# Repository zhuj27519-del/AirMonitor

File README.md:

# AirMonitor

环境监测器工程恢复与归档，整理日期：2026-11-12。统一工作目录：`D:\Projects\AirMonitor`。

## 原型机实拍

用户提供的 V4 原型机照片，拍摄日期及对应固件提交待确认。照片中可见 ONLINE 和各项读数；不代表测量精度或全部硬件验收已通过。更多照片见 [实物与装配记录](docs/images/prototype-v4/README.md)。

## 当前主源码

`src/AirMonitor/AirMonitor.ino` 原样恢复自 `AirMonitor_V4_9Text_Matched`，为 ESP8266 + HF035 九文本控件方案。选择依据为源码中明确的 0..8 页面控件映射和接线；不是仅按文件修改时间选择。它是待实物验证的工作基线，不代表已经量产或通过实测。

2026-11-12 使用本机 Arduino CLI、ESP8266 core 3.1.2、`esp8266:esp8266:nodemcuv2` 编译成功：RAM 28856/80192，IRAM 61895/65536，Flash 242752/1048576 字节。未烧录设备。

依赖 Arduino core 自带 Arduino.h、Wire（OLED 历史版）、EspSoftwareSerial；主源码未使用 Wi-Fi，也没有配置 Wi-Fi 密码。裸 ESP-12F 与 NodeMCU 不是同一种开发板：当前 D 引脚别名按 NodeMCU 定义，裸模块的启动电阻、电源、烧录方式需要核对。

## 配置与状态

|模块|主源码配置|证据及限制|
|---|---|---|
|ESP8266 / ESP-12F|按 NodeMCU ESP-12E 板型构建|模块型号来自任务；实际板载模块未现场确认|
|PMS7003M|TX→D5/GPIO14，9600 8N1|32 字节协议，读取大气环境 PM 字段；需真实帧验证|
|21VOC|TX→D6/GPIO12，9600 8N1|12 字节 0x2C 帧；负温度与量纲待核对|
|HF035|GPIO1 TX 输出，115200，212×318，sGUI 文本 ID 0..8|屏端 TX 标签含义需要按实际方向核实，不能仅凭标签将两个输出相连|
|OLED 历史方案|SDA D2/GPIO4，SCL D1/GPIO5|独立历史固件；不是当前 HF035 配置|

LCD/PMS 的 5V 供电说明来自历史代码；ESP8266 GPIO 为 3.3V 逻辑，实际信号电平和共地应核实。eCO2 是估算值，HCHO 是模块报告值。

发现的 STM32G0B1 + ST7789 分支、V1 首板与 KiCad 草稿分别归档，不能直接用于 ESP8266。历史硬件资料中的 NO-GO / DO NOT FABRICATE 状态仍有效。

## 开发

```powershell
arduino-cli core install esp8266:esp8266@3.1.2 --additional-urls https://arduino.esp8266.com/stable/package_esp8266com_index.json
arduino-cli compile --fqbn esp8266:esp8266:nodemcuv2 src/AirMonitor
```

本机验证使用已有 Arduino IDE 附带的 CLI 与 `.arduinoIDE/arduino-cli.yaml`，无需重装。构建不是硬件验收。IRAM 使用率 94%，增加功能前检查余量。

参见 [项目结构](docs/STRUCTURE.md)、[历史版本](docs/VERSIONS.md)、[检查报告](docs/AUDIT.md)、[TODO](TODO.md)。`docs/inventory.json` 记录来源、SHA-256 和目标路径；`docs/duplicates.json` 记录内容相同的文件。

原始目录未移动、未删除。压缩包、旧 Git bundle、订单 PDF、构建产物只在本地保留并排除 Git，避免未经检查的归档内容或订单隐私进入仓库。历史 CAD 工程保留目录完整性，不将共享文件强行合并。

## GitHub

公开仓库：https://github.com/zhuj27519-del/AirMonitor 。主分支为 main。首次上传已核对 commit SHA 与 tree SHA 一致；完整原始归档仍仅本地保存。

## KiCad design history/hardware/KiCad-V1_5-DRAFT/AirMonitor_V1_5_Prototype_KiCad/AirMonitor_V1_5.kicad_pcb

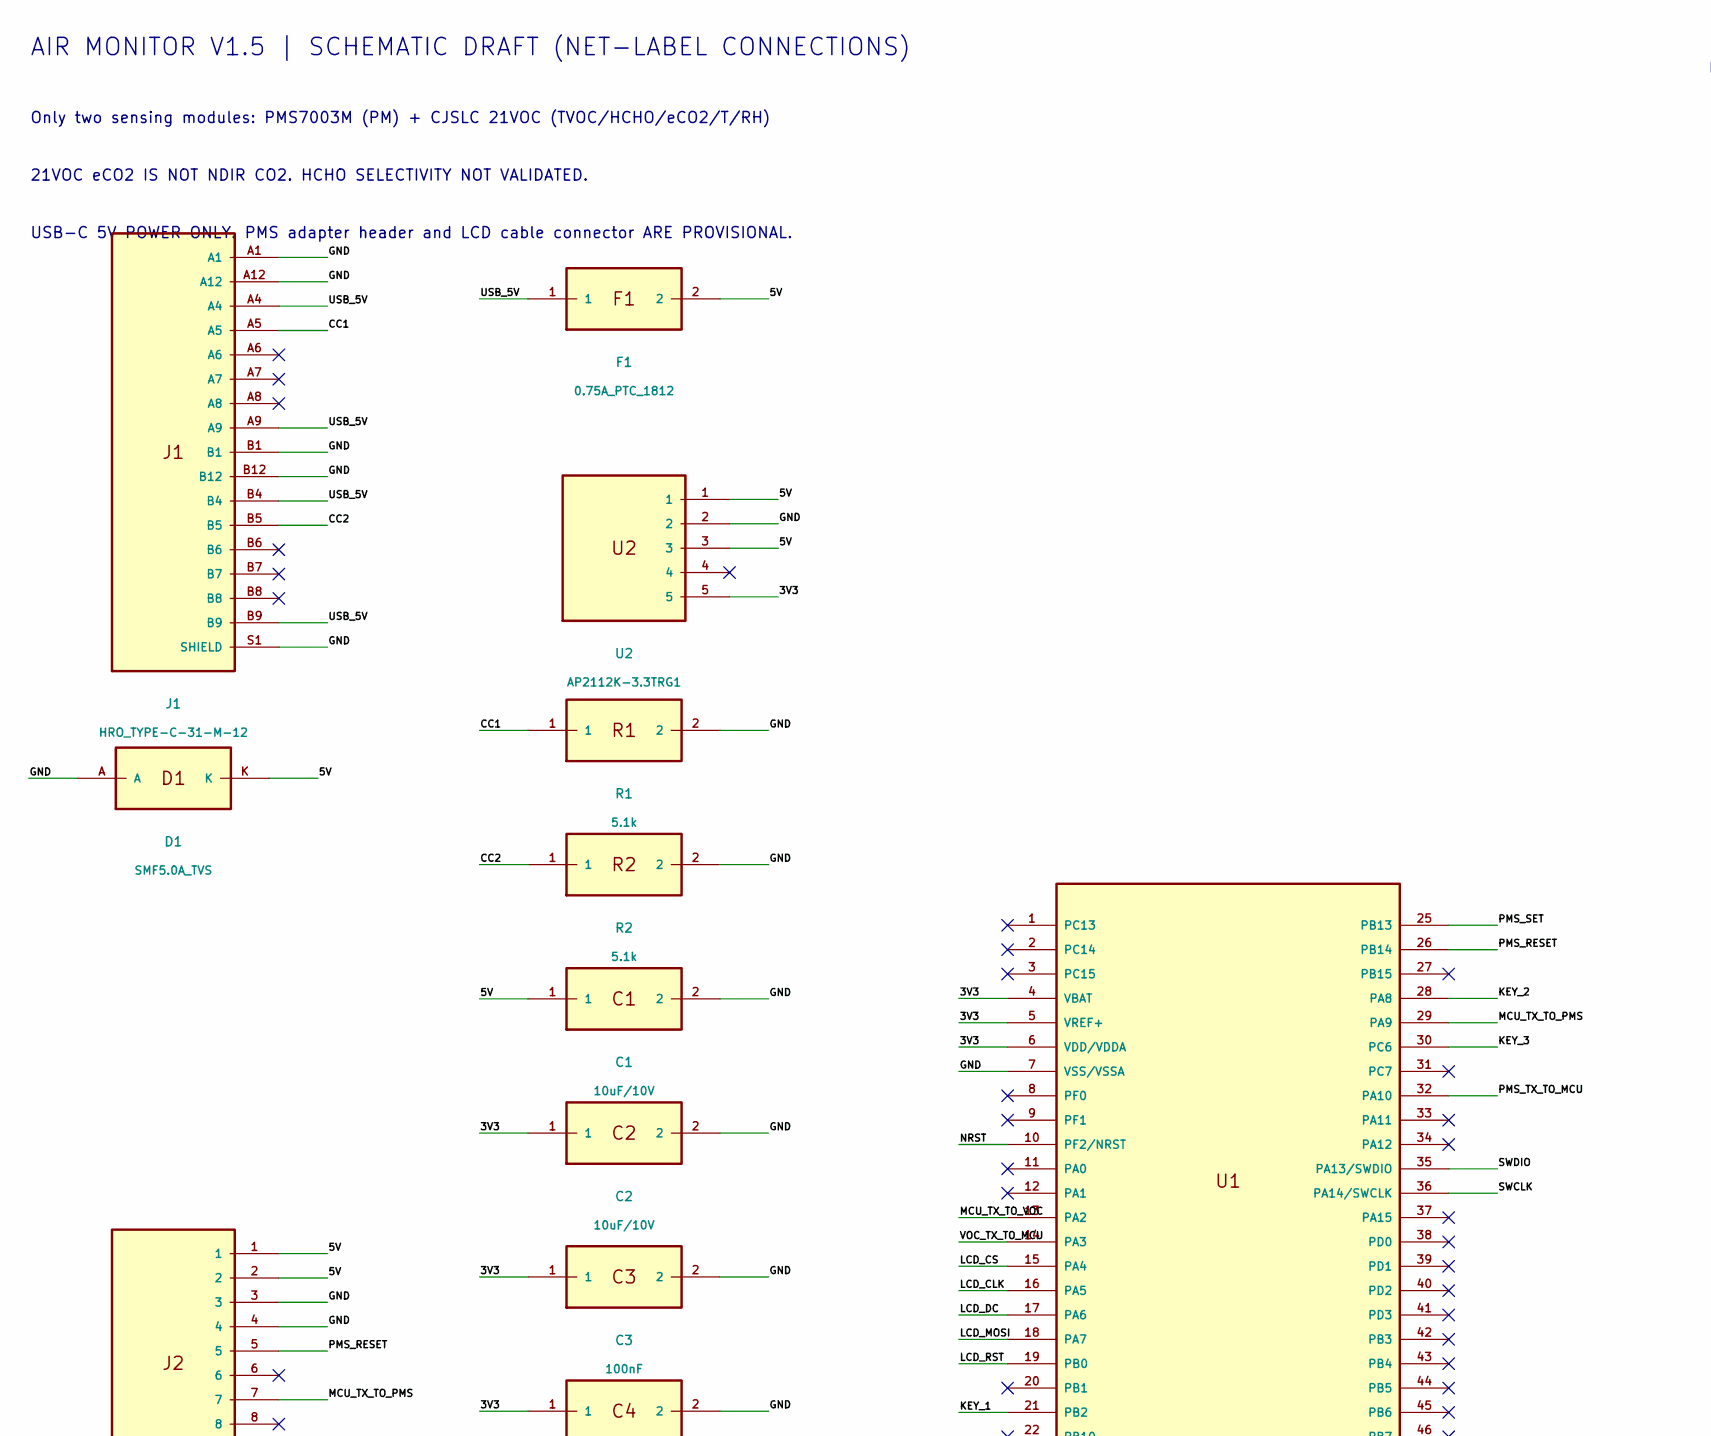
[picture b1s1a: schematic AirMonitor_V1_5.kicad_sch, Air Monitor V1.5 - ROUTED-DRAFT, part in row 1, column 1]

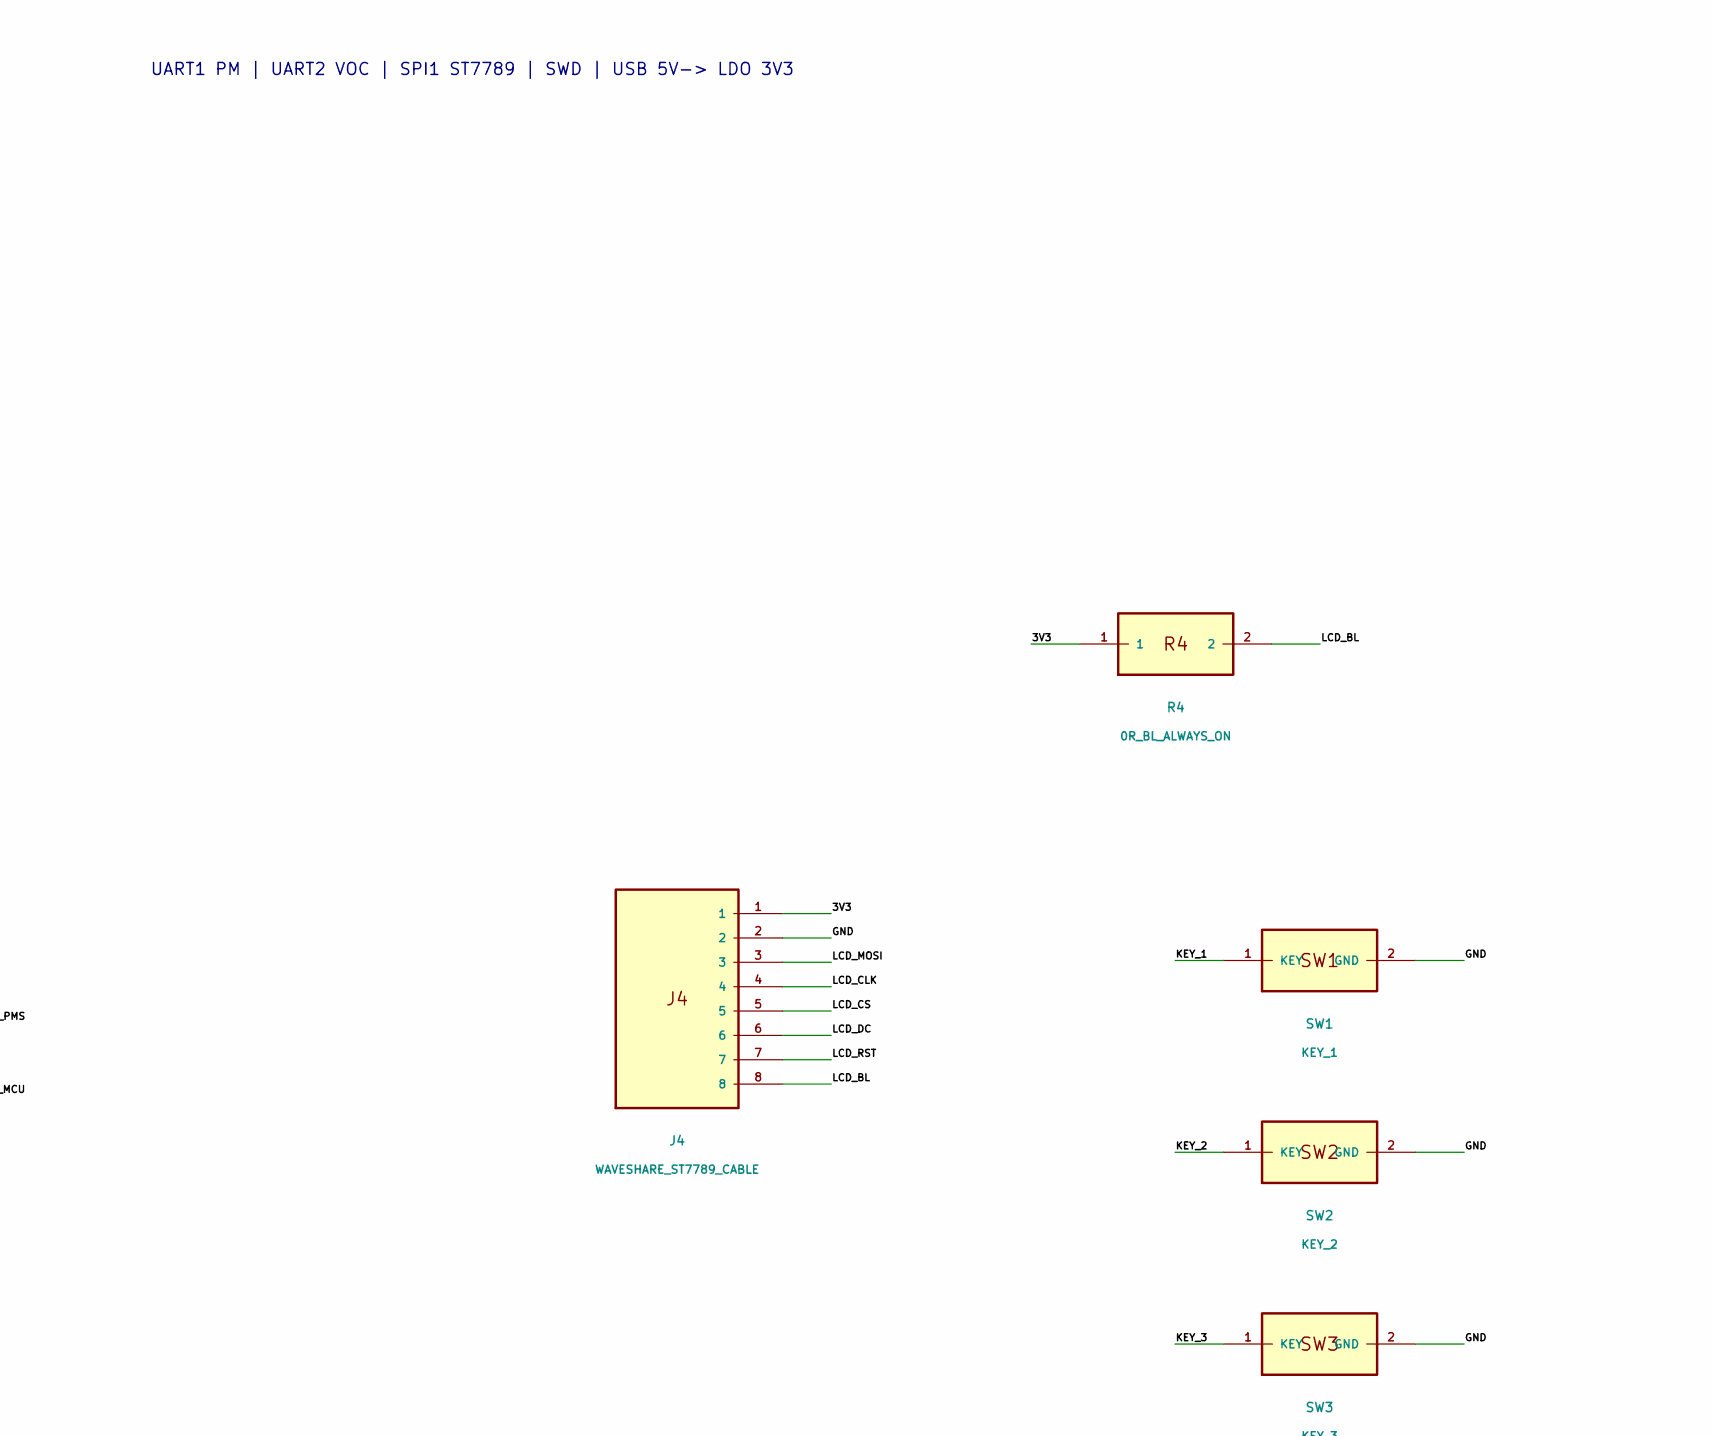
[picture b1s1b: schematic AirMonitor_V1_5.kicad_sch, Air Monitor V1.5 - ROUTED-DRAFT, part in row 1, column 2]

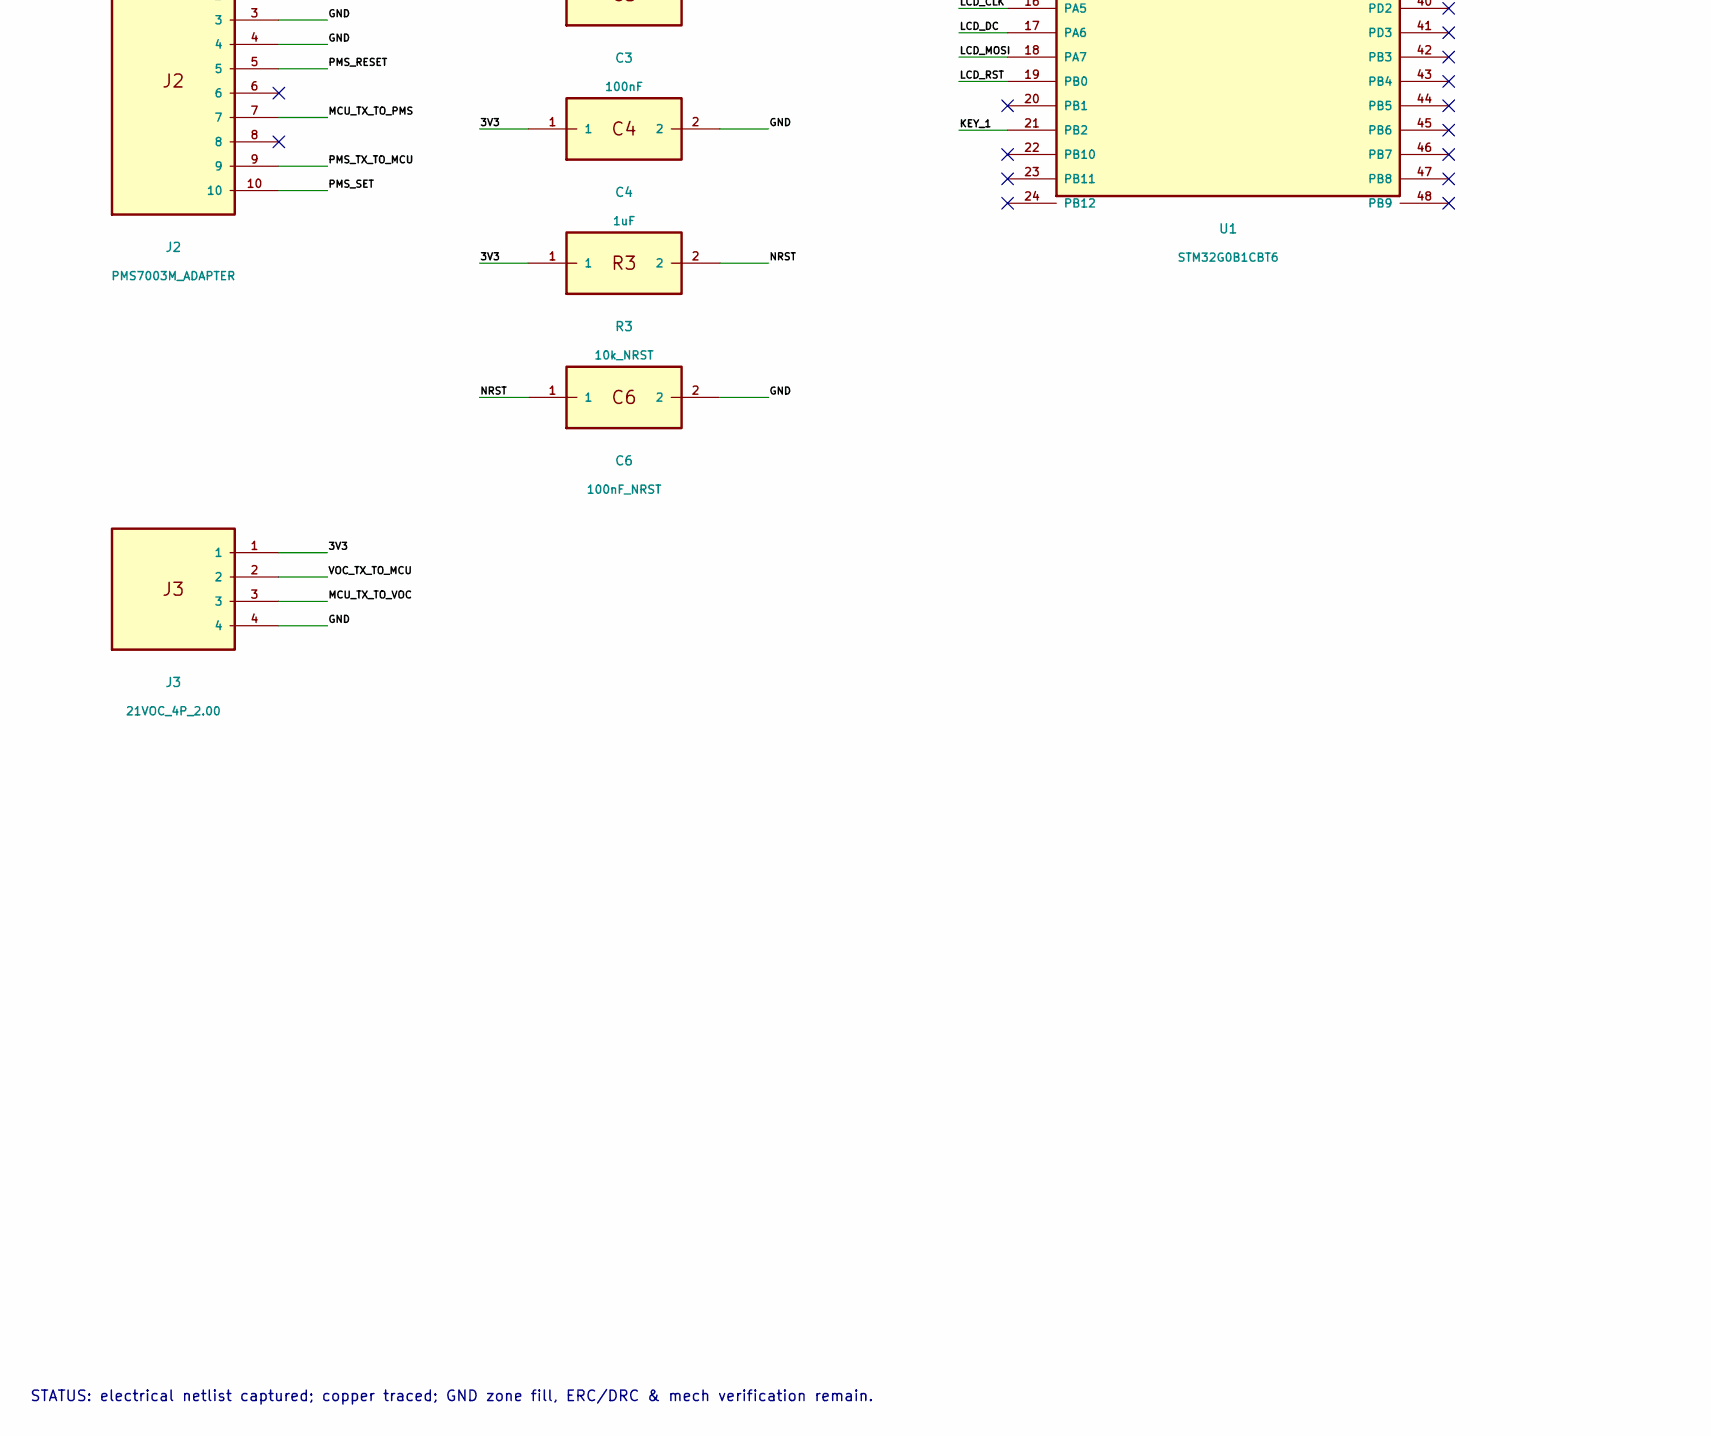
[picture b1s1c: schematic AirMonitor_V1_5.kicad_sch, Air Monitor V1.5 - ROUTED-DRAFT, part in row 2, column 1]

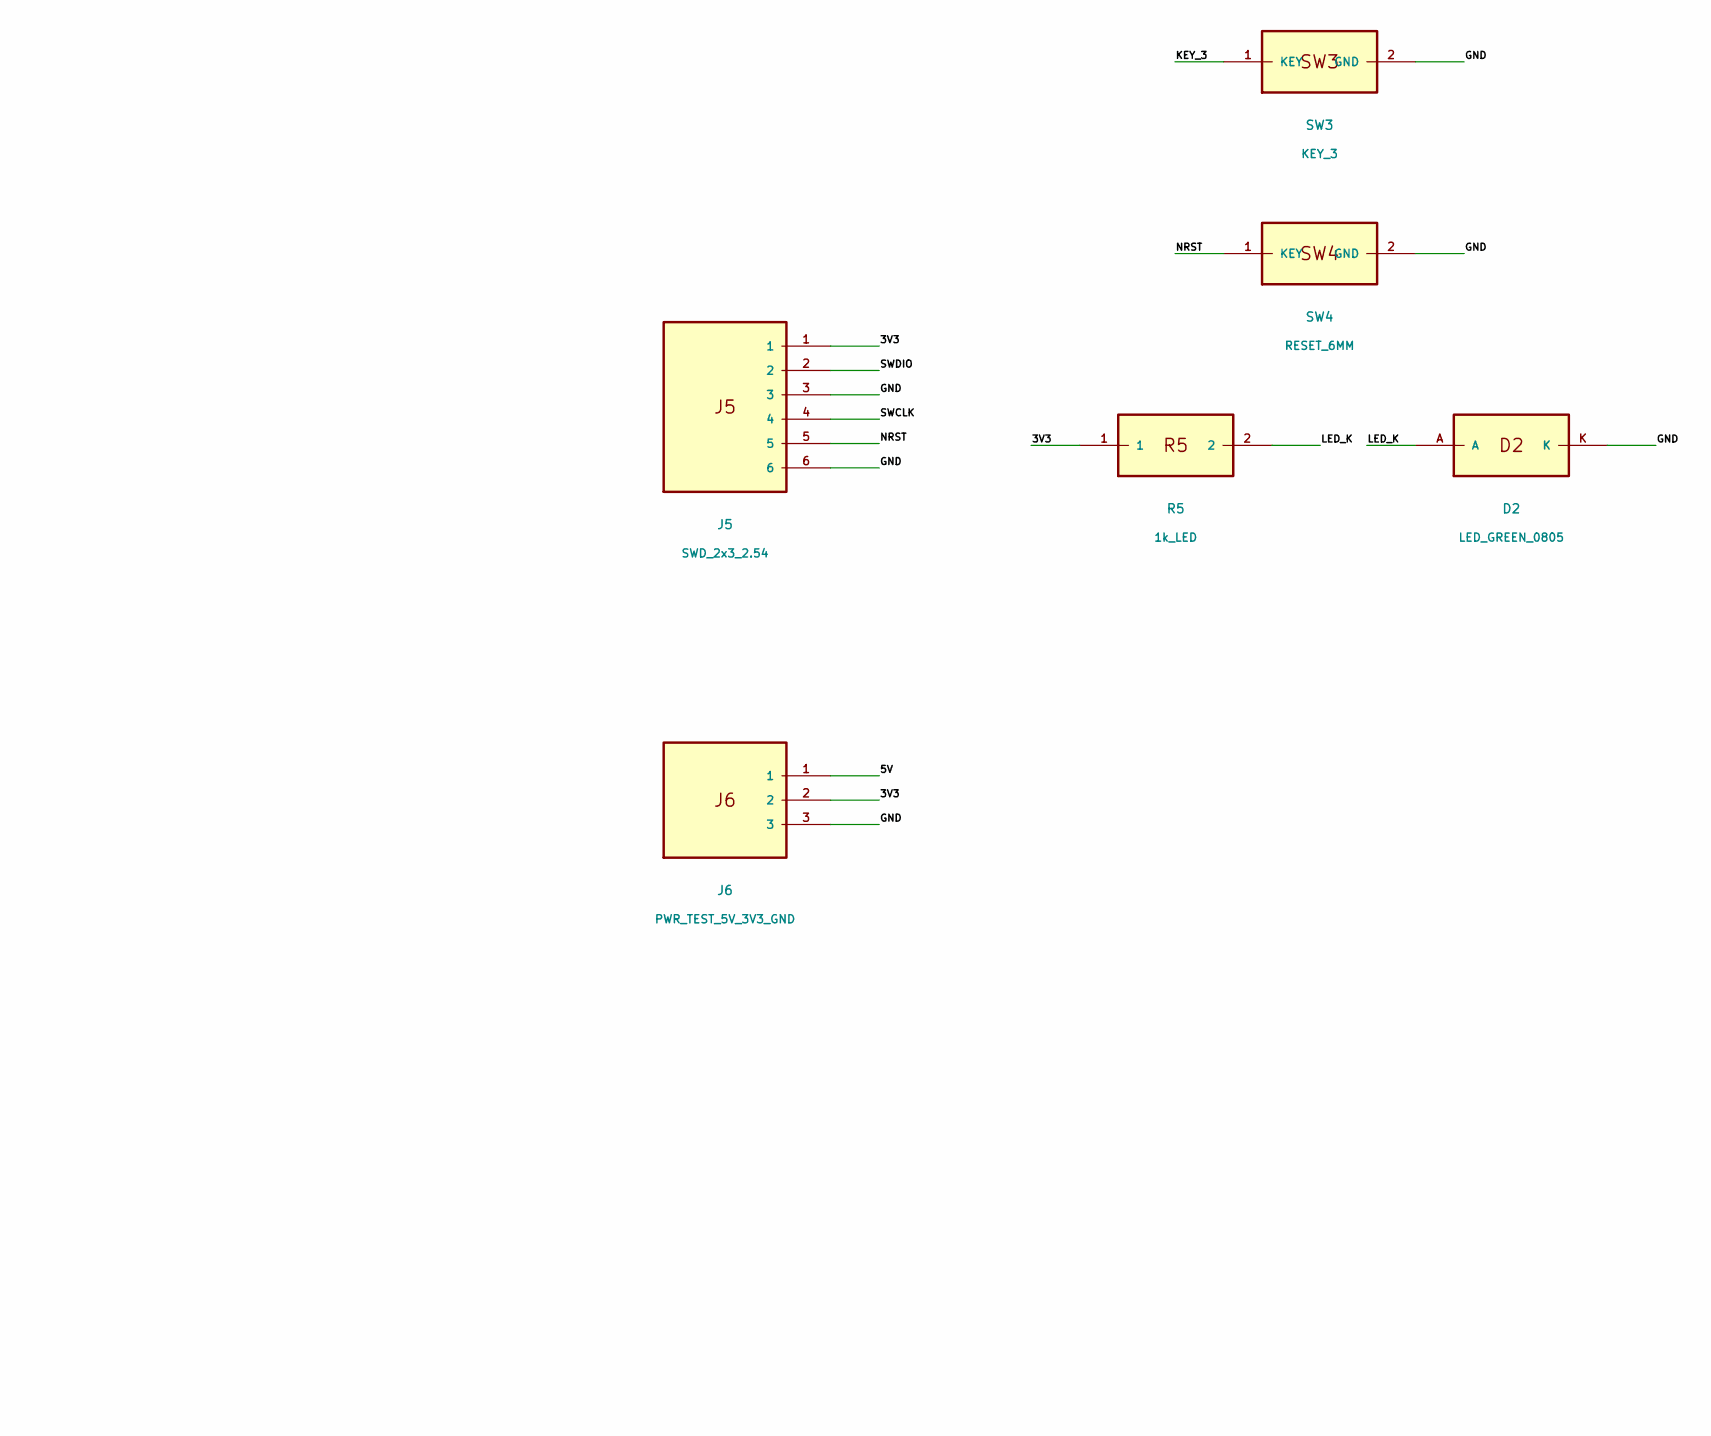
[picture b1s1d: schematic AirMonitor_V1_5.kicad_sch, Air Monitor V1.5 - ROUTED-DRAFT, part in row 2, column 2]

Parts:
C1, C2: 10uF/10V; 0805
C3: 100nF; 0805
C4: 1uF; 0805
C6: 100nF_NRST; 0805
D1: SMF5.0A_TVS; SOD123
D2: LED_GREEN_0805; LED_0805
F1: 0.75A_PTC_1812; 1812
J1: HRO_TYPE-C-31-M-12; USB_C_HRO
J2: PMS7003M_ADAPTER; PinHeader_2x05_2.54
J3: 21VOC_4P_2.00; PinHeader_1x04_2.00
J4: WAVESHARE_ST7789_CABLE; PinHeader_1x08_2.00
J5: SWD_2x3_2.54; PinHeader_2x03_2.54
J6: PWR_TEST_5V_3V3_GND; PinHeader_1x03_2.54
R1, R2: 5.1k; 0805
R3: 10k_NRST; 0805
R4: 0R_BL_ALWAYS_ON; 0805
R5: 1k_LED; 0805
SW1: KEY_1; SW_6x6mm_THT
SW2: KEY_2; SW_6x6mm_THT
SW3: KEY_3; SW_6x6mm_THT
SW4: RESET_6MM; SW_6x6mm_THT
U1: STM32G0B1CBT6; LQFP48_7x7_P0.5
U2: AP2112K-3.3TRG1; SOT23_5

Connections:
3V3: C2.1, C3.1, C4.1, J3.1, J4.1, J5.1, J6.2, R3.1, R4.1, R5.1, U1.4 (VBAT), U1.5 (VREF+), U1.6 (VDD/VDDA), U2.5
5V: C1.1, D1.K, F1.2, J2.1, J2.2, J6.1, U2.1, U2.3
CC1: J1.A5, R1.1
CC2: J1.B5, R2.1
GND: C1.2, C2.2, C3.2, C4.2, C6.2, D1.A, D2.K, J1.A1, J1.A12, J1.B1, J1.B12, J1.S1 (SHIELD), J2.3, J2.4, J3.4, J4.2, J5.3, J5.6, J6.3, R1.2, R2.2, SW1.2 (GND), SW2.2 (GND), SW3.2 (GND), SW4.2 (GND), U1.7 (VSS/VSSA), U2.2
KEY_1: SW1.1 (KEY), U1.21 (PB2)
KEY_2: SW2.1 (KEY), U1.28 (PA8)
KEY_3: SW3.1 (KEY), U1.30 (PC6)
LCD_BL: J4.8, R4.2
LCD_CLK: J4.4, U1.16 (PA5)
LCD_CS: J4.5, U1.15 (PA4)
LCD_DC: J4.6, U1.17 (PA6)
LCD_MOSI: J4.3, U1.18 (PA7)
LCD_RST: J4.7, U1.19 (PB0)
LED_K: D2.A, R5.2
MCU_TX_TO_PMS: J2.7, U1.29 (PA9)
MCU_TX_TO_VOC: J3.3, U1.13 (PA2)
NRST: C6.1, J5.5, R3.2, SW4.1 (KEY), U1.10 (PF2/NRST)
PMS_RESET: J2.5, U1.26 (PB14)
PMS_SET: J2.10, U1.25 (PB13)
PMS_TX_TO_MCU: J2.9, U1.32 (PA10)
SWCLK: J5.4, U1.36 (PA14/SWCLK)
SWDIO: J5.2, U1.35 (PA13/SWDIO)
USB_5V: F1.1, J1.A4, J1.A9, J1.B4, J1.B9
VOC_TX_TO_MCU: J3.2, U1.14 (PA3)

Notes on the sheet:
AIR MONITOR V1.5 | SCHEMATIC DRAFT (NET-LABEL CONNECTIONS)
Only two sensing modules: PMS7003M (PM) + CJSLC 21VOC (TVOC/HCHO/eCO2/T/RH)
21VOC eCO2 IS NOT NDIR CO2. HCHO SELECTIVITY NOT VALIDATED.
USB-C 5V POWER ONLY. PMS adapter header and LCD cable connector ARE PROVISIONAL.
STATUS: electrical netlist captured; copper traced; GND zone fill, ERC/DRC & mech verification remain.
UART1 PM | UART2 VOC | SPI1 ST7789 | SWD | USB 5V-> LDO 3V3

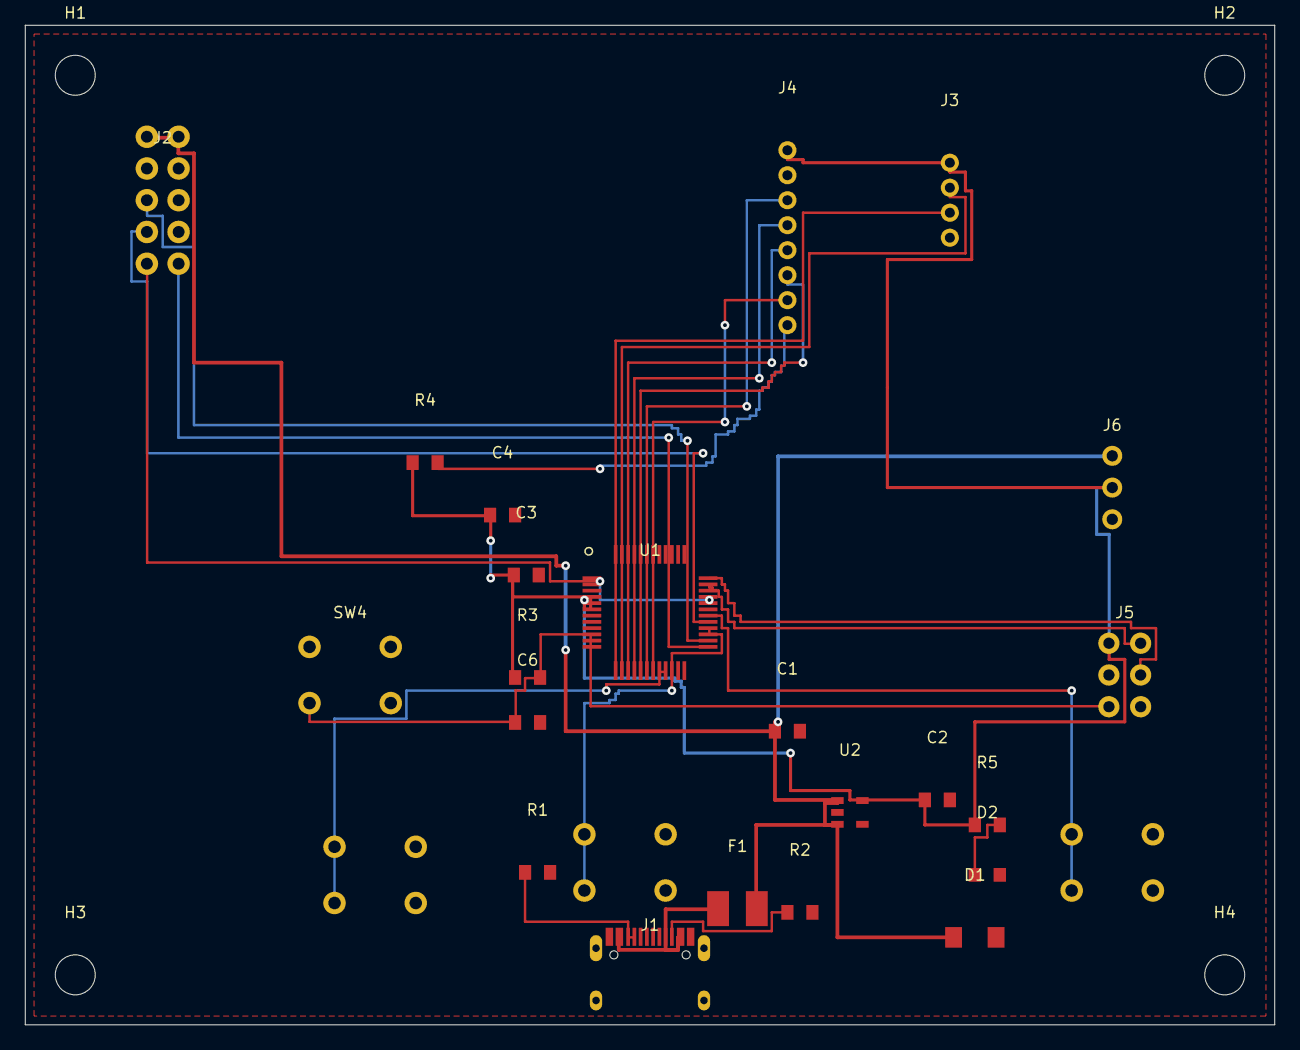
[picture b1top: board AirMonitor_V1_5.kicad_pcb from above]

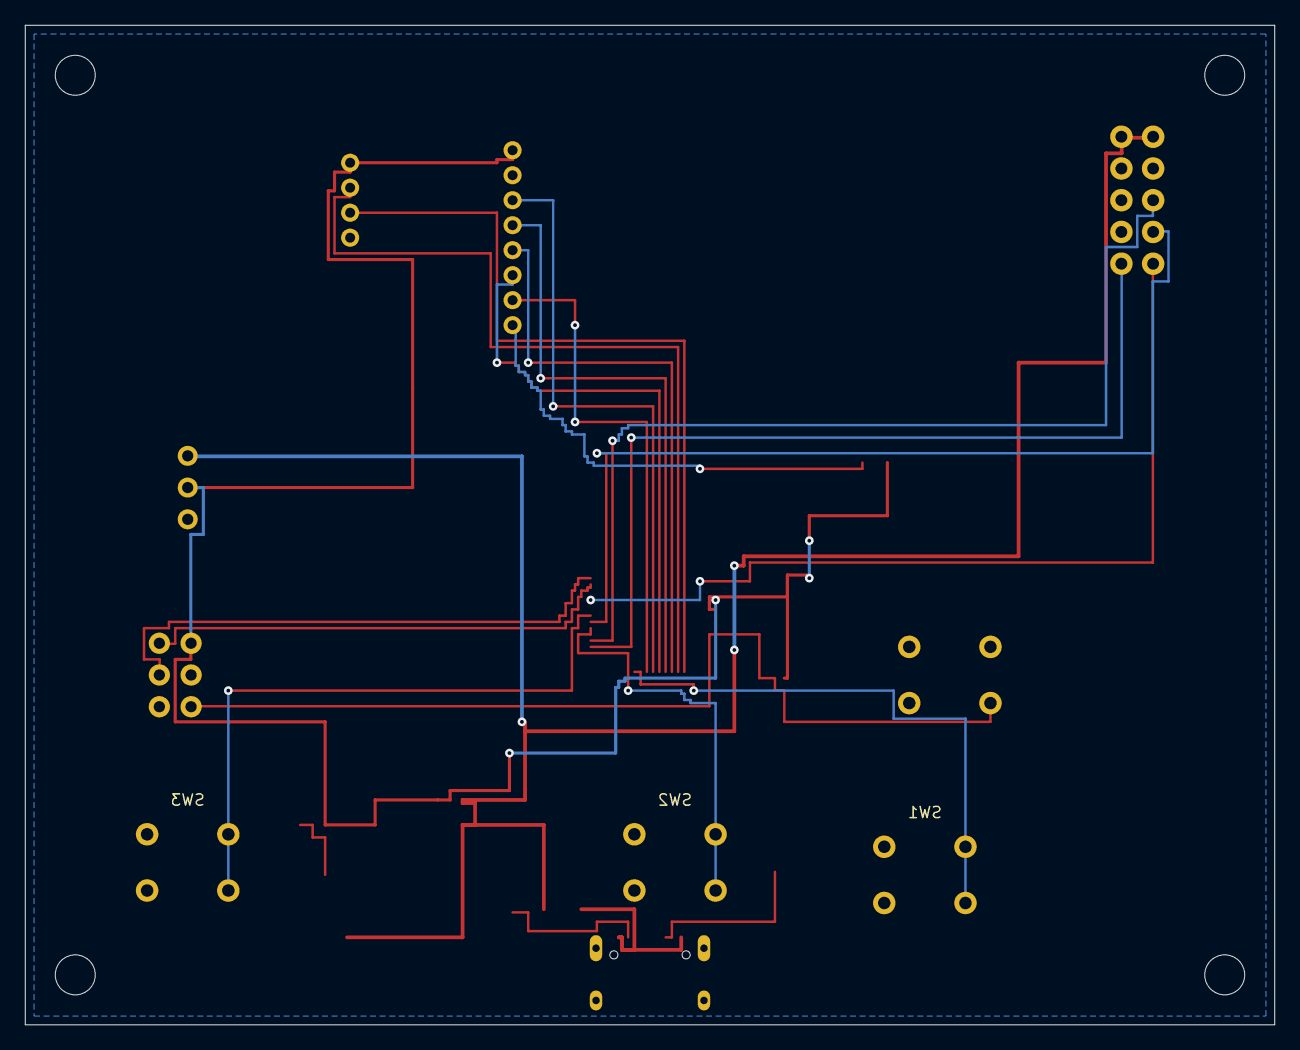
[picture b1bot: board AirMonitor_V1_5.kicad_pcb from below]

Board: 2 copper layers, 100.0 x 80.0 mm, 29 parts (3 on the bottom side), 25 nets.

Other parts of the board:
H1, H2, H3, H4: M3_NPTH; MountingHole_3.2

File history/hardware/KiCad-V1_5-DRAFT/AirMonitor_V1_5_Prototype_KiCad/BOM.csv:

Ref,Value,Footprint,Qty,Engineering note
U1,STM32G0B1CBT6,AirMonitor:LQFP48_7x7_P0.5,1,"STM32G0B1CBT6 (GP non-N) LQFP48 pinout cross-referenced against ST DS13560 Rev6 Fig5, VDD/VDDA, VBAT, VREF+ explicitly powered."
J1,HRO_TYPE-C-31-M-12,AirMonitor:USB_C_HRO,1,USB-C 5V power-only; verify HRO contact land-pattern against specific purchased connector. CURRENT PAD MODEL IS PROVISIONAL!
F1,0.75A_PTC_1812,AirMonitor:1812,1,
R1,5.1k,AirMonitor:0805,1,
R2,5.1k,AirMonitor:0805,1,
U2,AP2112K-3.3TRG1,AirMonitor:SOT23_5,1,
C1,10uF/10V,AirMonitor:0805,1,
C2,10uF/10V,AirMonitor:0805,1,
C3,100nF,AirMonitor:0805,1,
C4,1uF,AirMonitor:0805,1,
R3,10k_NRST,AirMonitor:0805,1,
C6,100nF_NRST,AirMonitor:0805,1,
D1,SMF5.0A_TVS,AirMonitor:SOD123,1,
J2,PMS7003M_ADAPTER,AirMonitor:PinHeader_2x05_2.54,1,"PMS7003M interface by adaptor cable, NOT native PMS connector. 5V/3V3 logic verification required on user module."
J3,21VOC_4P_2.00,AirMonitor:PinHeader_1x04_2.00,1,"21VOC 2.0mm side-port socket, per manufacturer. Align pin 1 to user datasheet; verify mechanical shape."
J4,WAVESHARE_ST7789_CABLE,AirMonitor:PinHeader_1x08_2.00,1,Waveshare 1.54 inch LCD SKU18079 2.0mm PH cable. J4 PCB male generic TH placeholder; replace with confirmed keyed connector before manufacturing.
R4,0R_BL_ALWAYS_ON,AirMonitor:0805,1,
J5,SWD_2x3_2.54,AirMonitor:PinHeader_2x03_2.54,1,
SW1,KEY_1,AirMonitor:SW_6x6mm_THT,1,
SW2,KEY_2,AirMonitor:SW_6x6mm_THT,1,
SW3,KEY_3,AirMonitor:SW_6x6mm_THT,1,
R5,1k_LED,AirMonitor:0805,1,
D2,LED_GREEN_0805,AirMonitor:LED_0805,1,
J6,PWR_TEST_5V_3V3_GND,AirMonitor:PinHeader_1x03_2.54,1,"3-pin test header for commissioning: 5V, 3V3, GND. Do not power board via multiple sources without isolation."
SW4,RESET_6MM,AirMonitor:SW_6x6mm_THT,1,"Reset button; pins on same side of tactile switch internally common, pins on other side common; verify actual body orientation."
H1,M3_NPTH,AirMonitor:MountingHole_3.2,1,
H2,M3_NPTH,AirMonitor:MountingHole_3.2,1,
H3,M3_NPTH,AirMonitor:MountingHole_3.2,1,
H4,M3_NPTH,AirMonitor:MountingHole_3.2,1,
